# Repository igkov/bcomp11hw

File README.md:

# bcomp11hw

Hardware made in KiCad software. This project of BCOMP11 hardware. Description on http://igorkov.org/bcomp11 and http://igorkov.org/bcomp11v2 pages.

Actual Gerber files here:
* Version 2.0 - http://igorkov.org/zip/bcomp11v2-gerber.zip
* Version 2.3 - http://igorkov.org/zip/bcomp11v2-gerber23.zip

Other information:
* [Using CAN-PHY drivers](https://github.com/igkov/bcomp11hw/wiki/CAN-PHY-drivers)
* [Using universal I/O](https://github.com/igkov/bcomp11hw/wiki/Universal-IO)
* [NMPS schemes](https://github.com/igkov/bcomp11hw/wiki/NMPS-schemes)

## Scheme:

## Board:

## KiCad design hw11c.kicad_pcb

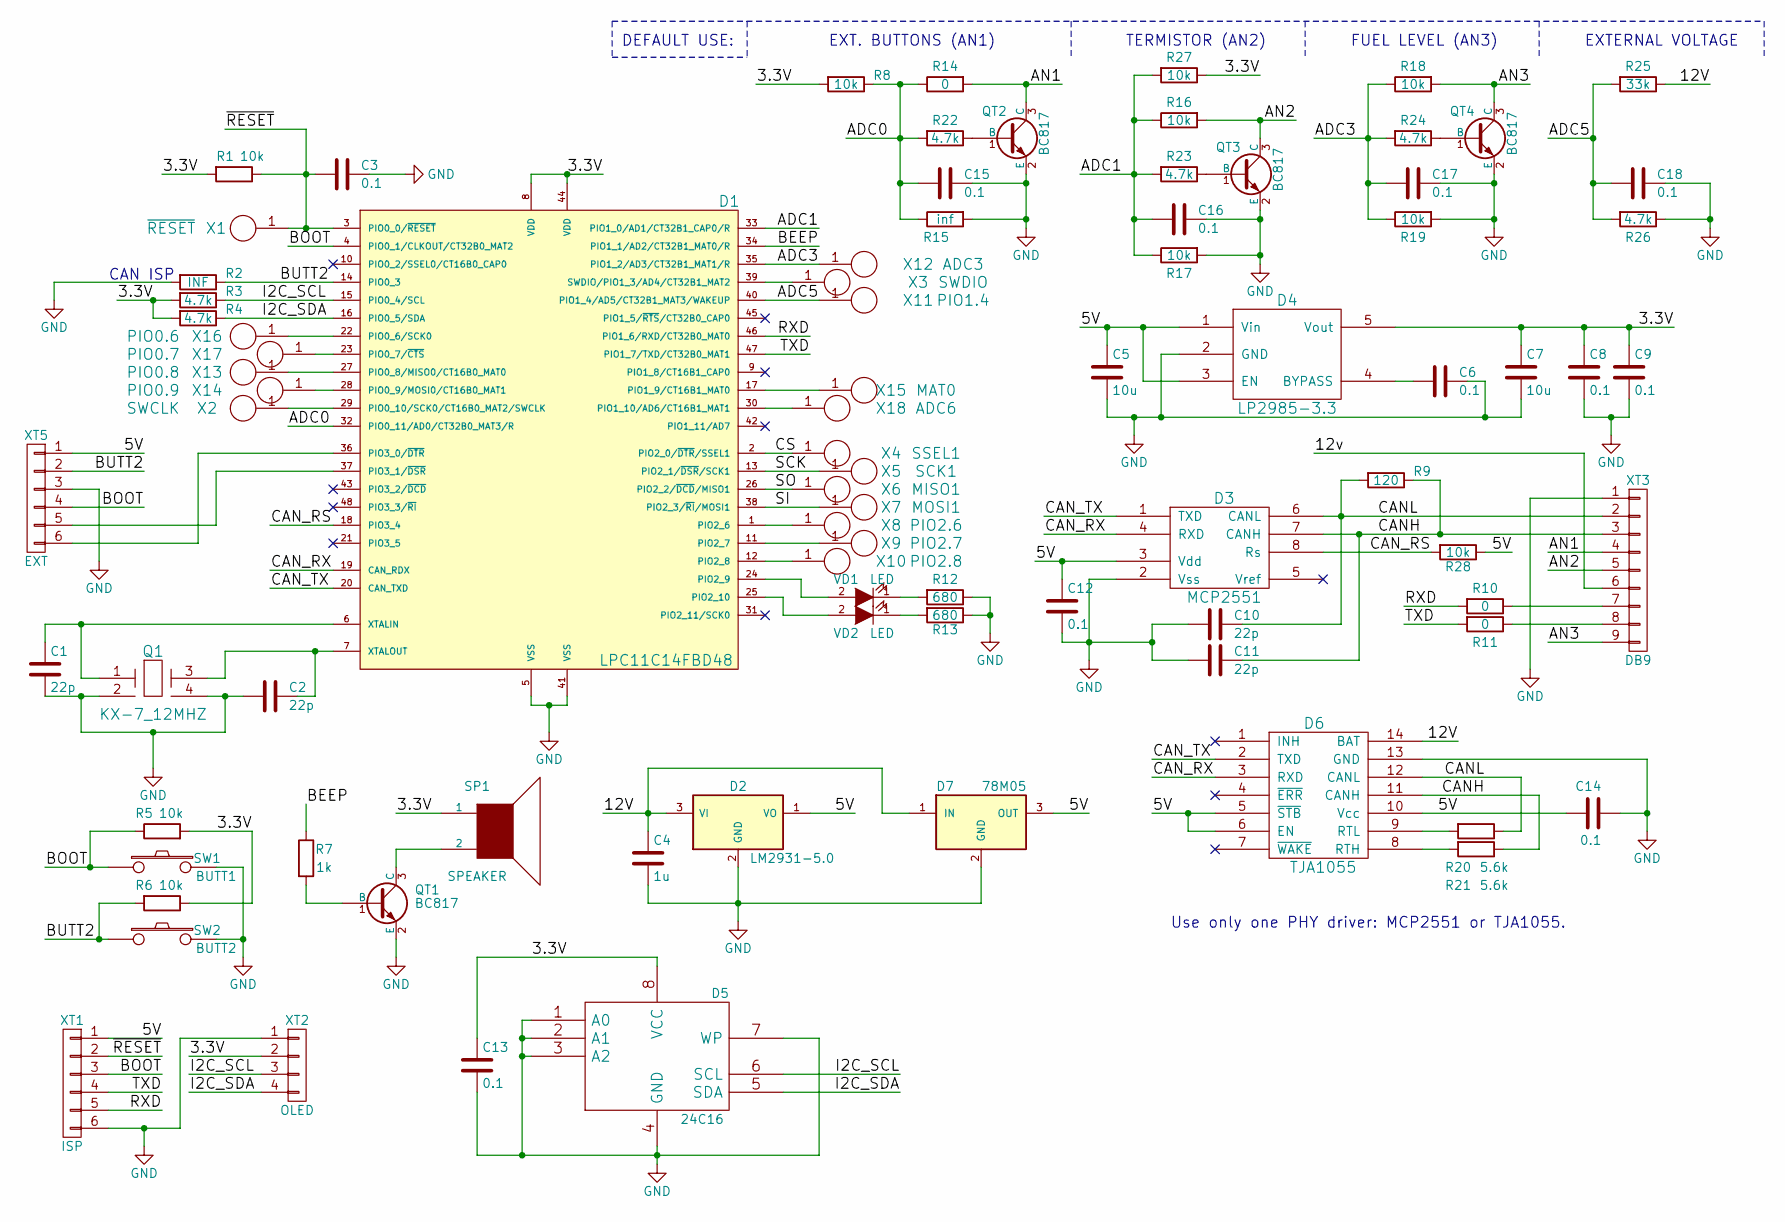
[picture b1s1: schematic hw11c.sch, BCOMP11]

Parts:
C1, C2, C10, C11: 22p; C_0603
C3, C6, C8, C9, C12, C13, C14, C15, C16, C17, C18: 0.1; C_0603
C4: 1u; C_1206
C5, C7: 10u; C_1206
D1: LPC11C14FBD48; LQFP-48_7x7mm_Pitch0.5mm
D2: LM2931-5.0; TO-92_Horizontal1_Inline_Narrow_Oval
D3: MCP2551; SOIC-8_3.9x4.9mm_Pitch1.27mm
D4: LP2985-3.3; SOT-23-5
D5: 24C16; SOIC-8_3.9x4.9mm_Pitch1.27mm
D6: TJA1055; SOIC-14_3.9x8.7mm_Pitch1.27mm
D7: 78M05; D-Pak_TO252AA
Q1: KX-7_12MHZ; KX-7
QT1, QT2, QT3, QT4: BC817; SOT-23
R1, R5, R6, R8, R16, R17, R18, R19, R27, R28: 10k; R_0603
R2: INF; R_0603
R3, R4, R22, R23, R24, R26: 4.7k; R_0603
R7: 1k; R_0603
R9: 120; R_0603
R10, R11, R14: 0; R_0603
R12, R13: 680; R_0603
R15: inf; R_0603
R20, R21: 5.6k; R_0603
R25: 33k; R_0603
SP1: SPEAKER; HC0901F
SW1: BUTT1; SW_SPST_FSMSM
SW2: BUTT2; SW_SPST_FSMSM
VD1, VD2: LED; LED-0603
X1: ~RESET; PAD
X2: SWCLK; PAD
X3: SWDIO; PAD
X4: SSEL1; PAD
X5: SCK1; PAD
X6: MISO1; PAD
X7: MOSI1; PAD
X8: PIO2.6; PAD
X9: PIO2.7; PAD
X10: PIO2.8; PAD
X11: PIO1.4; PAD
X12: ADC3; PAD
X13: PIO0.8; PAD
X14: PIO0.9; PAD
X15: MAT0; PAD
X16: PIO0.6; PAD
X17: PIO0.7; PAD
X18: ADC6; PAD
XT1: ISP; Pin_Header_Angled_1x06
XT2: OLED; OLED_I2C
XT3: DB9; DB9M_CI
XT5: EXT; Pin_Header_Straight_1x06

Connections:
/3.3V: C7.1, C8.1, C9.1, C13.1, D1.8 (VDD), D1.44 (VDD), D4.5 (Vout), D5.8 (VCC), R1.2, R3.2, R4.2, R5.2, R6.1, R8.2, R27.1, SP1.1, XT2.2
/5V: C5.1, C12.1, C14.1, D2.1 (VO), D3.3 (Vdd), D4.1 (Vin), D4.3 (EN), D6.5 (~STB), D6.6 (EN), D6.10 (Vcc), D7.3 (OUT), R28.1, XT1.1, XT5.1
/12V: C4.1, D2.3 (VI), D6.14 (BAT), D7.1 (IN), R25.1, XT3.6
/ADC0: C15.2, D1.32 (PIO0_11/AD0/CT32B0_MAT3/R), R8.1, R14.1, R15.1, R22.2
/ADC1: C16.2, D1.33 (PIO1_0/AD1/CT32B1_CAP0/R), R16.1, R17.1, R23.2, R27.2
/ADC3: C17.2, D1.35 (PIO1_2/AD3/CT32B1_MAT1/R), R18.1, R19.1, R24.2, X12.1
/ADC5: C18.2, D1.40 (PIO1_4/AD5/CT32B1_MAT3/WAKEUP), R25.2, R26.2, X11.1
/AN1: QT2.3 (C), R14.2, XT3.4
/AN2: QT3.3 (C), R16.2, XT3.5
/AN3: QT4.3 (C), R18.2, XT3.9
/BEEP: D1.34 (PIO1_1/AD2/CT32B1_MAT0/R), R7.1
/BOOT: D1.4 (PIO0_1/CLKOUT/CT32B0_MAT2), R5.1, SW1.1, XT1.3, XT5.4
/BUTT2: D1.14 (PIO0_3), R2.1, R6.2, SW2.1, XT5.2
/CANH: C11.1, D3.7 (CANH), D6.11 (CANH), R9.1, R21.1, XT3.3
/CANL: C10.1, D3.6 (CANL), D6.12 (CANL), R9.2, R20.1, XT3.2
/CAN_RS: D1.18 (PIO3_4), D3.8 (Rs), R28.2
/CAN_RX: D1.19 (CAN_RDX), D3.4 (RXD), D6.3 (RXD)
/CAN_TX: D1.20 (CAN_TXD), D3.1 (TXD), D6.2 (TXD)
/CS: D1.2 (PIO2_0/~DTR~/SSEL1), X4.1
/I2C_SCL: D1.15 (PIO0_4/SCL), D5.6 (SCL), R3.1, XT2.3
/I2C_SDA: D1.16 (PIO0_5/SDA), D5.5 (SDA), R4.1, XT2.4
/RXD: D1.46 (PIO1_6/RXD/CT32B0_MAT0), R10.2, XT1.5
/SCK: D1.13 (PIO2_1/~DSR~/SCK1), X5.1
/SI: D1.38 (PIO2_3/~RI~/MOSI1), X7.1
/SO: D1.26 (PIO2_2/~DCD~/MISO1), X6.1
/TXD: D1.47 (PIO1_7/TXD/CT32B0_MAT1), R11.2, XT1.4
/~RESET: C3.2, D1.3 (PIO0_0/~RESET~), R1.1, X1.1, XT1.2
GND: C1.2, C2.2, C3.1, C4.2, C5.2, C6.1, C7.2, C8.2, C9.2, C10.2, C11.2, C12.2, C13.2, C14.2, C15.1, C16.1, C17.1, C18.1, D1.5 (VSS), D1.41 (VSS), D2.2 (GND), D3.2 (Vss), D4.2 (GND), D5.1 (A0), D5.2 (A1), D5.3 (A2), D5.4 (GND), D5.7 (WP), D6.13 (GND), D7.2 (GND), Q1.2, Q1.4, QT1.2 (E), QT2.2 (E), QT3.2 (E), QT4.2 (E), R2.2, R12.1, R13.1, R15.2, R17.2, R19.2, R26.1, SW1.2, SW2.2, XT1.6, XT2.1, XT3.1, XT5.3
unnamed: C1.1, D1.6 (XTALIN), Q1.1
unnamed: C2.1, D1.7 (XTALOUT), Q1.3
unnamed: C6.2, D4.4 (BYPASS)
unnamed: D1.1 (PIO2_6), X8.1
unnamed: D1.11 (PIO2_7), X9.1
unnamed: D1.12 (PIO2_8), X10.1
unnamed: D1.17 (PIO1_9/CT16B1_MAT0), X15.1
unnamed: D1.22 (PIO0_6/SCK0), X16.1
unnamed: D1.23 (PIO0_7/~CTS~), X17.1
unnamed: D1.24 (PIO2_9), VD1.2 (A)
unnamed: D1.25 (PIO2_10), VD2.2 (A)
unnamed: D1.27 (PIO0_8/MISO0/CT16B0_MAT0), X13.1
unnamed: D1.28 (PIO0_9/MOSI0/CT16B0_MAT1), X14.1
unnamed: D1.29 (PIO0_10/SCK0/CT16B0_MAT2/SWCLK), X2.1
unnamed: D1.30 (PIO1_10/AD6/CT16B1_MAT1), X18.1
unnamed: D1.36 (PIO3_0/~DTR~), XT5.6
unnamed: D1.37 (PIO3_1/~DSR~), XT5.5
unnamed: D1.39 (SWDIO/PIO1_3/AD4/CT32B1_MAT2), X3.1
unnamed: D6.8 (RTH), R21.2
unnamed: D6.9 (RTL), R20.2
unnamed: QT1.1 (B), R7.2
unnamed: QT1.3 (C), SP1.2
unnamed: QT2.1 (B), R22.1
unnamed: QT3.1 (B), R23.1
unnamed: QT4.1 (B), R24.1
unnamed: R10.1, XT3.7
unnamed: R11.1, XT3.8
unnamed: R12.2, VD1.1 (K)
unnamed: R13.2, VD2.1 (K)

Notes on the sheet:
CAN ISP
Use only one PHY driver: MCP2551 or TJA1055.
EXT. BUTTONS (AN1)
TERMISTOR (AN2)
EXTERNAL VOLTAGE
FUEL LEVEL (AN3)
DEFAULT USE:

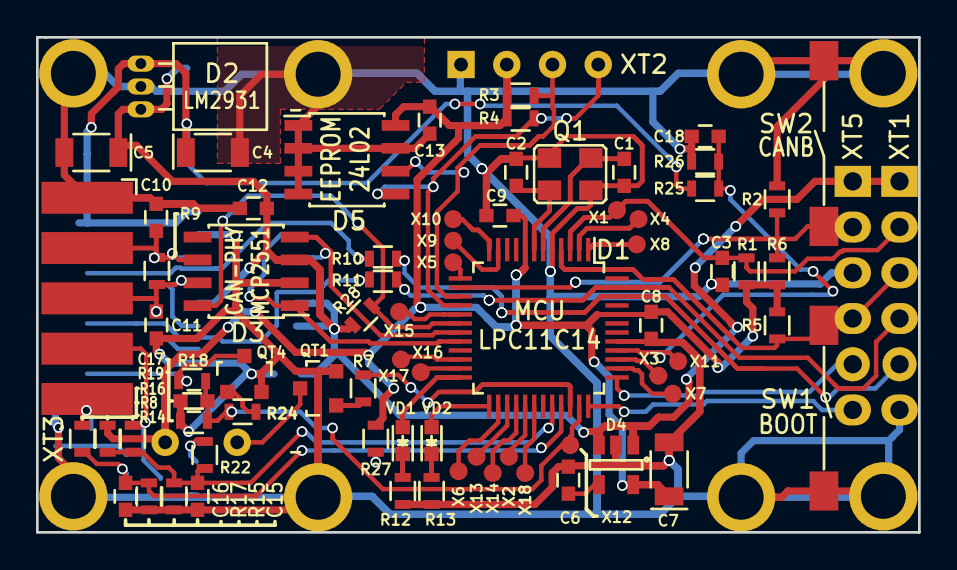
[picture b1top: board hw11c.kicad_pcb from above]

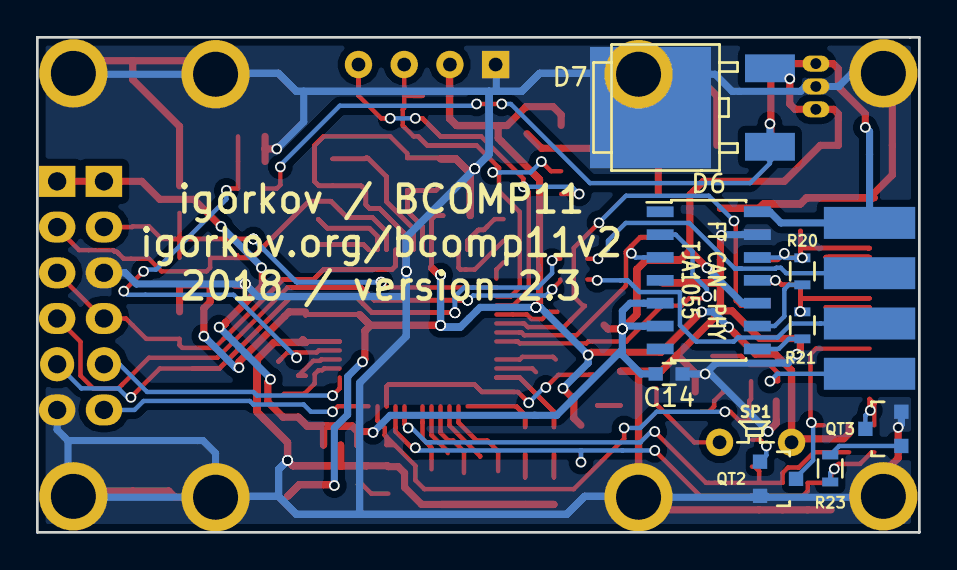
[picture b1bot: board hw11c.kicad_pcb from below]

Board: 2 copper layers, 49.0 x 27.5 mm, 85 parts (9 on the bottom side), 57 nets.

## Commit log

2017-12-19 add all project files
2017-12-19 Add author information to board.
2017-12-21 Add termistor support in AN1 channel. Fix silk layer in board.
2017-12-22 Add AN3 channel on board.
2017-12-27 Add connector for external buttons.
2018-01-18 Replace XT4 to XT5, more pins in connector (P3.0 and P3.1 to extern).
2018-01-19 Add R10, R11 to RX and TX lines.
2018-01-22 Add X16/X17 pads. Fix buttons silk.
2018-02-02 Add holes at the edges of the board.
2018-02-02 New board size: 49x27.5mm.
2018-02-02 Sizes in brd vision.
2018-02-05 Add TJA1055 (Fault-tolerant CAN) on board. This PHY use in some CAN-BODY (comfort bus).
2018-02-05 Version 2.1 commit.
2018-02-06 Add fault-tolerance CAN PHY: TJA1055. Version of board 2.1.
2018-02-06 Fix C5 position.
2018-02-16 Add open-drain outs (shared with analog input). Version 2.3.
2018-02-19 Update pictures
2018-02-20 Fix silk layer. Add wiki links.
2018-03-01 Add links to Gerber-files.
2018-04-11 Fix SO-14 case for TJA-1055.
2018-04-11 Add LM78M05 to board. It used as alternate DC-DC for applications with current consumption more 100mA.
2018-06-08 Add todo-list file.
2018-06-09 Add resistive divider on ADC5 (AIN4) for system voltage measurement. Add reference voltage for AIN2. Add information on scheme.
2018-06-09 Clear TODO.md. Fix capasitors on scheme.
2018-06-27 Add X18 pad.
2018-07-19 Add Rs signal for MCP2551. Pin connected to MCU pin 3.4.
